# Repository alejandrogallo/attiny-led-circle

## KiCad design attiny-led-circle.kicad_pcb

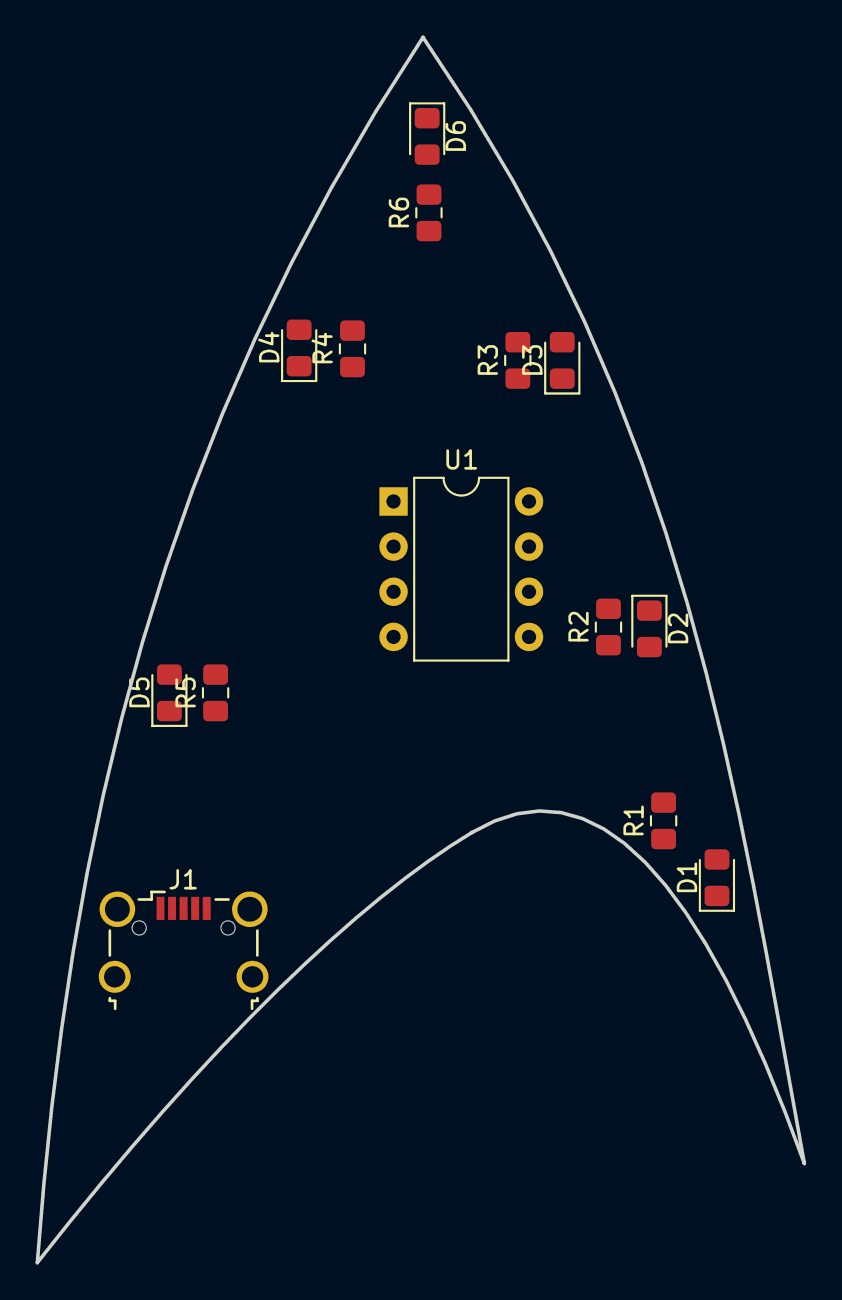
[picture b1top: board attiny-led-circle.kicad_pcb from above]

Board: 2 copper layers, 43.1 x 68.9 mm, 15 parts (1 on the bottom side), 14 nets, no tracks yet.

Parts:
BT1: Battery_Cell; BatteryHolder_Keystone_1056TR
D1, D2, D3, D4, D5, D6: LED; LED_0805_2012Metric_Pad1.15x1.40mm_HandSolder
J1: USB_B_Micro; USB_Micro-B_Wuerth_629105150521_CircularHoles
R1, R2, R3, R4, R5, R6: R; R_0805_2012Metric_Pad1.15x1.40mm_HandSolder
U1: ATtiny13A-PU; DIP-8_W7.62mm

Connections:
GND: BT1.2, J1.5, U1.4
LED1: D1.1, U1.5
LED2: D2.1, U1.6
LED3: D3.1, U1.7
LED4: D4.1, U1.2
LED5: D5.1, U1.3
LED6: D6.1, U1.1
unnamed: D1.2, R1.2
unnamed: D2.2, R2.2
unnamed: D3.2, R3.2
unnamed: D4.2, R4.2
unnamed: D5.2, R5.2
unnamed: D6.2, R6.2
VCC: BT1.1, J1.1, R1.1, R2.1, R3.1, R4.1, R5.1, R6.1, U1.8

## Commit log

2019-08-27 add lib
2019-08-28 Add Emblem
